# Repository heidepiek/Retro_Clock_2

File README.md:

# Retro Clock 2

This is a personal customized version of the original ESP32 Pacman Clock project.  
I've added some visual and functional enhancements to suit my own preferences.

### My additions:
- Blinking dots between hours and minutes
- Rectangle around the time
- Date and day display
- Text below the time: “ESP32 Pacman Clock”
- Pacman and ghost icons

The rest of this README reflects the original project, which deserves full credit for the excellent foundation.

# Retro_Clock_2
 Improved version of Retro_Clock
 1. Redesigned all of clock case parts with freeCAD. results in cleaner parts.
 2. All STL files are from freeCAD redesign.
 3. Minor firmware changes. Added menu items.
 4. PCB redesign to use better audio amplifier.
 
# Retro_Clock
This is a highly modified version of TechKiwiGadgets clock found on 

1. Instructables     https://www.instructables.com/ESP32-Pacman-Clock/
2. Makerbot Thingiverse (ESP32 Pacman Clock)    https://www.thingiverse.com/thing:5136672

Modifications:
1. Changed TFT display to an SPI version which has a much improved Touch interface.
2. Added SPIFFS to support files for data and images. This freed up memory and added flexability.
3. Added support for optional RTC (real time clock IC). Improves time keeping accuracy.
4. Added support for LDR (light dependent resistor) so that display is dimmed at night.
5. Added audio amplifier (LM386) and volume control via touch screen.
6. Redesigned user interface (Touch menu) to support added features.
7. Made many changes to firmware to improve speed and readability. 
8. Designed PCB to support above mentioned changes.
9. Redesigned 3D printed parts to support hardware changes.

TFT_eSPI library:
1. The TFT_eSPI library requires it be changed to support each particular build (unusal but that's way way it works).
2. The file User_Setup_Select.h specifies which setup file in the User_Setups directory is to be used.
3. Added to the User_Setups directory is the file Setup_Pacman_Clock.h which contains the specifies the configuration and features (Touch) used by this project.
4. Move the file "Setup_Pacman_Clock.h" into directory   ...Arduino/libraries/TFT_eSPI/User_Setups
5. Move the file "User_Setup_Select.h" into the directory    ...Arduino/libraries/TFT_eSPI   (replaces the existing User_Setup_Select.h file). 

Tools:
1. Arduino IDE 1.8.19, Board: DOIT ESP32 DEVKIT V1
2. Initialize SPIFFS using Arduino IDE  "Tools/ESP32 Sketch Data Upload" (which will initializee SPIFFS and upload all the files from the Data directory).
3. Creality Slicer, PLA, 0.2mm, no supports.

Additional Notes:
1. 	Arduino Sketch (IDE) Version 1.8.19
2.	Board Manager -> esp32 by Espressif Systems Version 1.0.6
3.	Libraries used:

		TFT_eSPI at version 2.5.0
		RTClib at version 2.1.1
		Wire at version 1.0.1
		SPIFFS at version 1.0
		FS at version 1.0
		XT_DAC_Audio
		Time at version 1.6.1
		Adafruit_BusIO at version 1.14.1
4.	TFT_eSPI setup file contains (see TFT_eSPI folder in Arduino/libraries):

		#define USER_SETUP_ID 900
		#define ILI9341_DRIVER
		#define TFT_MISO	19
		#define TFT_MOSI	23
		#define TFT_SCLK	18
		#define TFT_CS		15
		#define TFT_DC		4
		#define TFT_RST		2

		#define TOUCH_CS	5		// Required to enable Touch, getTouch()

		#define LOAD_GLCD
		#define LOAD_FONT2
		#define LOAD_FONT4
		#define LOAD FONT6
		#define LOAD_FONT7
		#define LOAD_FONT8
		#define LOAD_GFXFF
		#define SMOOTH_FONT

		#define SPI_FREQUENCY 27000000					// 27 MHz
		#define SPI_READ_FREQUENCY 20000000				// 20 MHz
		#define SPI_TOUCH_FREQUENCY 2500000				// 2.5 MHz

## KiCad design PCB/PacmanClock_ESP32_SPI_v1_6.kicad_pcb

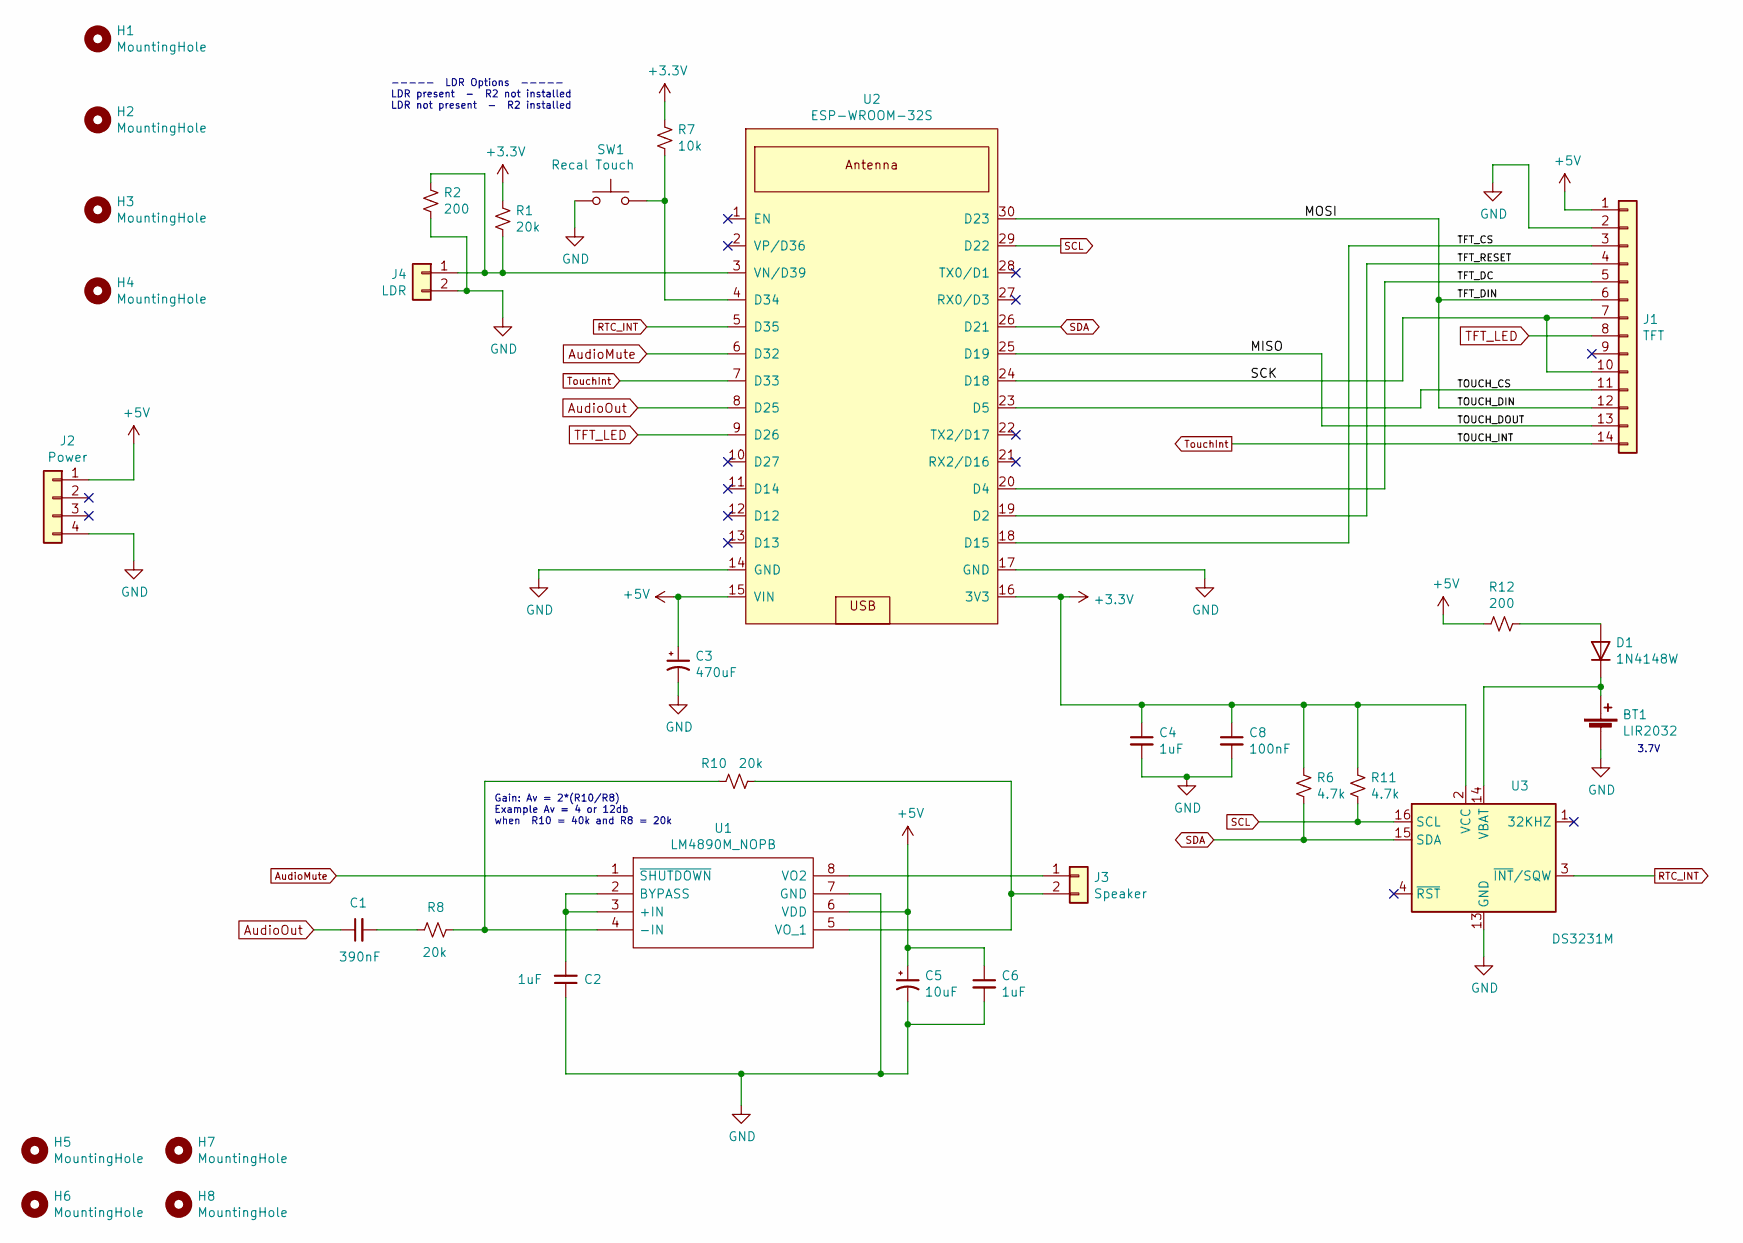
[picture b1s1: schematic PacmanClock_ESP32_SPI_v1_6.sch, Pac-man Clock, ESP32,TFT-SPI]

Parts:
BT1: LIR2032; 2032BatteryHolderHoriz
C1: 390nF; C_0805_2012Metric_Pad1.18x1.45mm_HandSolder
C2, C4: 1uF; C_1206_3216Metric_Pad1.33x1.80mm_HandSolder
C3: 470uF; CP_Radial_D8.0mm_P3.50mm
C5: 10uF; CP_Radial_D4.0mm_P1.50mm
C6: 1uF; C_0805_2012Metric_Pad1.18x1.45mm_HandSolder
C8: 100nF; C_0805_2012Metric_Pad1.18x1.45mm_HandSolder
D1: 1N4148W; D_SOD-123
H1, H2, H3, H4, H5, H6, H7, H8: MountingHole; MountingHole_2.7mm_M2.5_DIN965
J1: TFT; PinSocket_1x14_P2.54mm_Vertical
J2: Power; JST_XH_B4B-XH-A_1x04_P2.50mm_Vertical
J3: Speaker; JST_XH_B2B-XH-A_1x02_P2.50mm_Vertical
J4: LDR; JST_XH_B2B-XH-A_1x02_P2.50mm_Vertical
R1, R8, R10: 20k; R_0805_2012Metric_Pad1.20x1.40mm_HandSolder
R2, R12: 200; R_0805_2012Metric_Pad1.20x1.40mm_HandSolder
R6, R11: 4.7k; R_0805_2012Metric_Pad1.20x1.40mm_HandSolder
R7: 10k; R_0805_2012Metric_Pad1.20x1.40mm_HandSolder
SW1: Recal Touch; FSM2JRT_gm
U1: LM4890M_NOPB; SOIC-8_3.9x4.9mm_P1.27mm; Manufacturer_Part_Number LM4890M/NOPB; Mouser Part Number 926-LM4890M/NOPB
U2: ESP-WROOM-32S
U3: DS3231M; SOIC-16W_7.5x10.3mm_P1.27mm

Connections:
+3V3: C4.1, C8.1, R1.1, R6.1, R7.1, R11.1, U2.16 (3V3), U3.2 (VCC)
+5V: C3.1, C5.1, C6.1, J1.1, J2.1, R12.2, U1.6 (VDD), U2.15 (VIN)
/MISO: J1.13, U2.25 (D19)
/MOSI: J1.6, J1.12, U2.30 (D23)
/SCK: J1.7, J1.10, U2.24 (D18)
/TFT_CS: J1.3, U2.18 (D15)
/TFT_DC: J1.5, U2.20 (D4)
/TFT_RESET: J1.4, U2.19 (D2)
/TOUCH_CS: J1.11, U2.23 (D5)
AudioMute: U1.1 (~SHUTDOWN), U2.6 (D32)
AudioOut: C1.1, U2.8 (D25)
GND: BT1.2 (-), C2.1, C3.2, C4.2, C5.2, C6.2, C8.2, J1.2, J2.4, J4.2, R2.2, SW1.1, U1.7 (GND), U2.14 (GND), U2.17 (GND), U3.5 (GND), U3.6 (GND), U3.7 (GND), U3.8 (GND), U3.9 (GND), U3.10 (GND), U3.11 (GND), U3.12 (GND), U3.13 (GND)
unnamed: BT1.1 (+), D1.1 (K), U3.14 (VBAT)
unnamed: C1.2, R8.2
unnamed: C2.2, U1.2 (BYPASS), U1.3 (+IN)
unnamed: D1.2 (A), R12.1
unnamed: J3.1, U1.8 (VO2)
unnamed: J3.2, R10.2, U1.5 (VO_1)
unnamed: J4.1, R1.2, R2.1, U2.3 (VN/D39)
unnamed: R7.2, SW1.2, U2.4 (D34)
unnamed: R8.1, R10.1, U1.4 (-IN)
RTC_INT: U2.5 (D35), U3.3 (~INT~/SQW)
SCL: R11.2, U2.29 (D22), U3.16 (SCL)
SDA: R6.2, U2.26 (D21), U3.15 (SDA)
TFT_LED: J1.8, U2.9 (D26)
TouchInt: J1.14, U2.7 (D33)

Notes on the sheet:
3.7V
Gain: Av = 2*(R10/R8) Example Av = 4 or 12db when R10 = 40k and R8 = 20k
----- LDR Options ----- LDR present - R2 not installed LDR not present - R2 installed

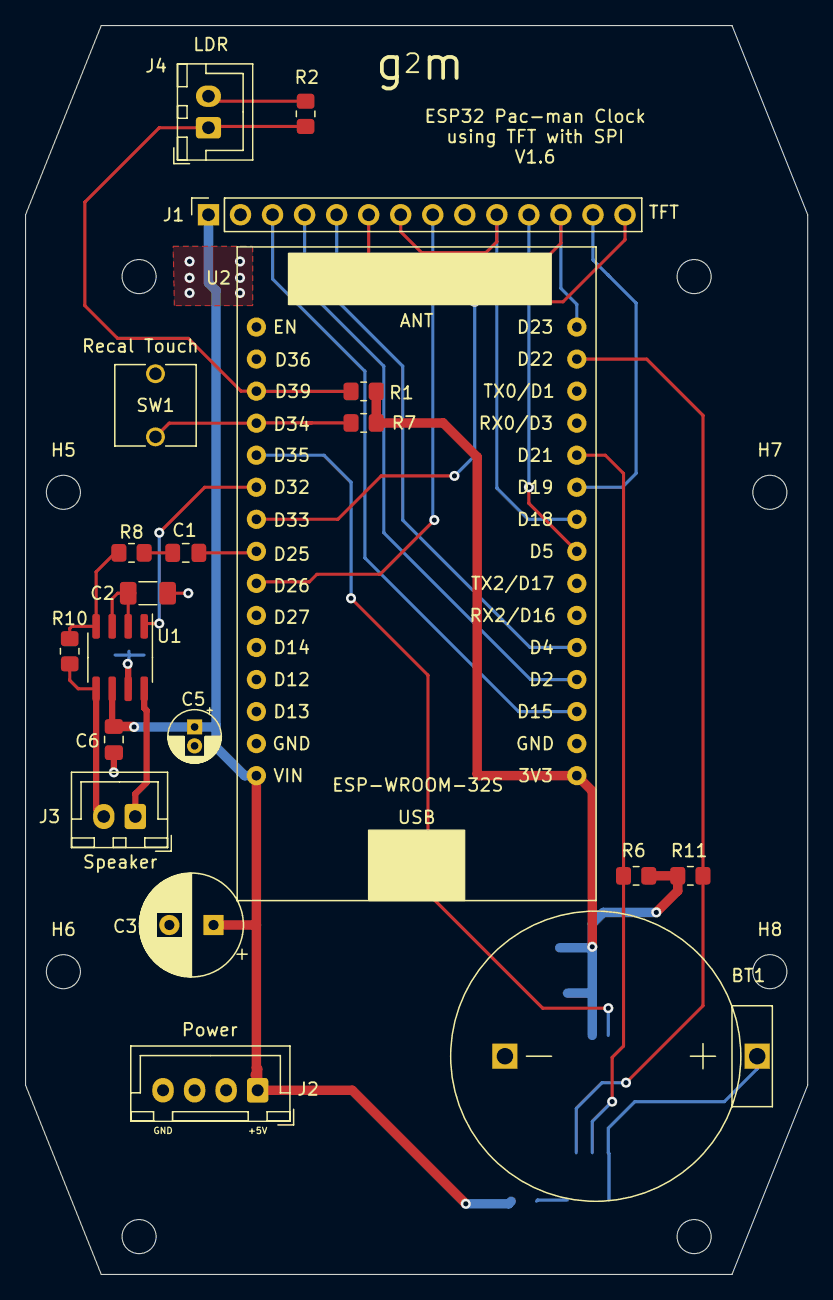
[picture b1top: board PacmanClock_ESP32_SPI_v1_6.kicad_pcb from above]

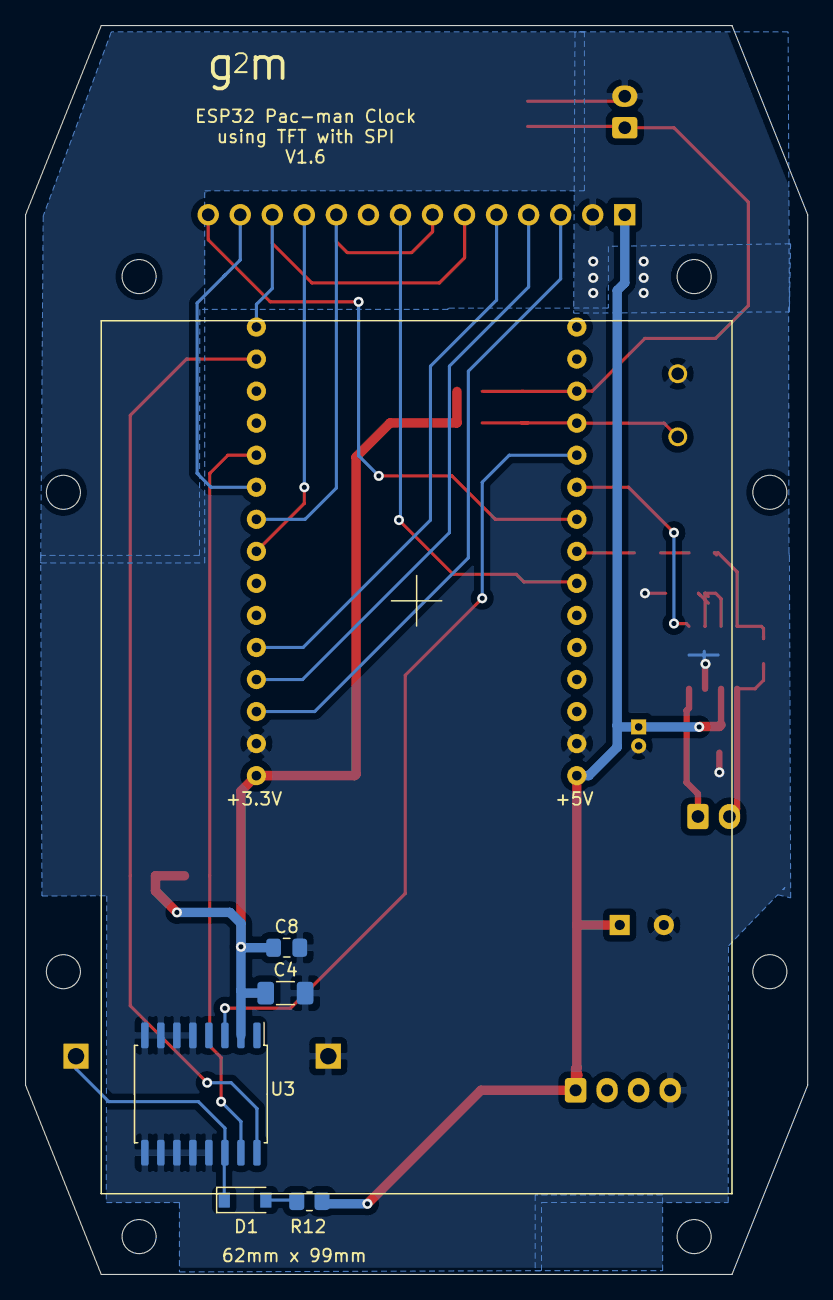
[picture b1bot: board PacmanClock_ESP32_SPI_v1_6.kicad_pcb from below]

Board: 2 copper layers, 62.0 x 99.0 mm, 33 parts (5 on the bottom side), 26 nets.

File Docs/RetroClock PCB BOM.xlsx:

Retro Clock 2
Component Count: | 33
Ref | Value | Footprint | Amazon (search) | Notes
BT1 | Holder | KiCab_g2m_Lib:2032BatteryHolderHoriz |  | See note on U3,. Used battery holder from DS3231 board.
C1 | 390nF | Capacitor_SMD:C_0805_2012Metric_Pad | 0805 SMD Capacitor Assorted Kit 1pF-1uF Chip Ceramic Capacitor
C2 | 1uF | Capacitor_SMD:C_1206_3216Metric_Pad | 1206 SMD Capacitor Assorted Kit 10P-22UF Chip Ceramic Capacitor
C3 | 470uF | Capacitor_THT:CP_Radial_D8.0mm_P3.50mm | lectrolytic Capacitor 470uF 16V with Aluminum Radial Leads 470UF-16V-8X12
C4 | 1uF | Capacitor_SMD:C_1206_3216Metric_Pad | 1206 SMD Capacitor Assorted Kit 10P-22UF Chip Ceramic Capacitor
C5 | 10uF | Capacitor_THT:CP_Radial_D4.0mm_P1.50mm | Electrolytic Capacitor 10uF 25V with Aluminum Radial Leads 10UF-25V-4X7
C6 | 1uF | Capacitor_SMD:C_0805_2012Metric_Pad | 0805 SMD Capacitor Assorted Kit 1pF-1uF Chip Ceramic Capacitor
C8 | 100nF | Capacitor_SMD:C_0805_2012Metric_Pad | 0805 SMD Capacitor Assorted Kit 1pF-1uF Chip Ceramic Capacitor
D1 | 1N4148W | Diode_SMD:D_SOD-123 |  | See U3. Used diode from DS3231 board.
H1 | MountingHole | MountingHole:MountingHole_2.7mm_M2.5_DIN965
H2 | MountingHole | MountingHole:MountingHole_2.7mm_M2.5_DIN965
H3 | MountingHole | MountingHole:MountingHole_2.7mm_M2.5_DIN965
H4 | MountingHole | MountingHole:MountingHole_2.7mm_M2.5_DIN965
H5 | MountingHole | MountingHole:MountingHole_2.7mm_M2.5_DIN965
H6 | MountingHole | MountingHole:MountingHole_2.7mm_M2.5_DIN965
H7 | MountingHole | MountingHole:MountingHole_2.7mm_M2.5_DIN965
H8 | MountingHole | MountingHole:MountingHole_2.7mm_M2.5_DIN965
J1 | TFT Connector | Connector_PinSocket_2.54mm:PinSocket_1x14_P2.54mm_Vertical | 40 Pin 2.54mm Single Row Straight Female PCB Header Connector Strip | Cut strip to required length - 14 pins.
J2 | Power | Connector_JST:JST_XH_B4B-XH-A_1x04_P2.50mm_Vertical | JST-XH 2.54mm Connector Kit, 2.54mm Male and Female 2/3/4/5/6 Pin Header Housin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
J3 | Speaker | Connector_JST:JST_XH_B2B-XH-A_1x02_P2.50mm_Vertical | JST-XH 2.54mm Connector Kit, 2.54mm Male and Female 2/3/4/5/6 Pin Header Housin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
J4 | LDR | Connector_JST:JST_XH_B2B-XH-A_1x02_P2.50mm_Vertical | JST-XH 2.54mm Connector Kit, 2.54mm Male and Female 2/3/4/5/6 Pin Header Housin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
R1 | 20k | Resistor_SMD:R_0805_2012Metric_Pad | 0805 SMD Resistor Kit 0-10M Ω ohm
R2 | 200 | Resistor_SMD:R_0805_2012Metric_Pad | 0805 SMD Resistor Kit 0-10M Ω ohm | Only installed if LDR option is not used.
R6 | 4.7k | Resistor_SMD:R_0805_2012Metric_Pad | 0805 SMD Resistor Kit 0-10M Ω ohm
R7 | 10k | Resistor_SMD:R_0805_2012Metric_Pad | 0805 SMD Resistor Kit 0-10M Ω ohm
R8 | 20k | Resistor_SMD:R_0805_2012Metric_Pad | 0805 SMD Resistor Kit 0-10M Ω ohm
R10 | 20k | Resistor_SMD:R_0805_2012Metric_Pad | 0805 SMD Resistor Kit 0-10M Ω ohm
R11 | 4.7k | Resistor_SMD:R_0805_2012Metric_Pad | 0805 SMD Resistor Kit 0-10M Ω ohm
R12 | 200 | Resistor_SMD:R_0805_2012Metric_Pad | 0805 SMD Resistor Kit 0-10M Ω ohm
SW1 | Recal Touch | Tactile-switch:FSM2JRT_gm | 6x6x7mm 2 Pin Panel PCB Momentary Tactile Tact Push Button Switch Through Hole 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
U1 | LM4890M_NOPB | Package_SO:SOIC-8_3.9x4.9mm_P1.27mm |  | Mouser: 926-LM4890M/NOPB
U2 | ESP-WROOM-32S | If Socketed (recommended) - uses two of the following connectors Connector_PinS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 | 40 Pin 2.54mm Single Row Straight Female PCB Header Connector Strip | Cut strip to required length - 15 pins. Quantity 2.
U3 | DS3231M | Package_SO:SOIC-16W_7.5x10.3mm_P1.27mm | DS3231 AT24C32 Clock Module Real Time Clock Module IIC RTC Module | Ordering from Amazon is much less expensive. Although you will need to remove t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
Plug-in Devices
Battery | LIR2032 | Rechargeable 2032 Battery, 3.7V | LIR2032 Rechargeable Batteries 3.7V with High Capacity 70mA
TFT |  | 2.8 inch TFT with Touch, SPI interface. | ILI9341 2.8" SPI TFT LCD Display Touch Panel 240X320
ESP32S | ESP32S | ESP32S Module - 30 pins (2 rows of 15 pins) | ESP-WROOM-32 ESP32 ESP-32S Development Board 2.4GHz Dual-Mode WiFi + Bluetooth 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
Hardware
Screws - 6mm Qty 9 |  | Torx Plus Rounded Head Thread-Forming Screws for Plastic, Zinc-Plated Steel, M2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 | McMaster-Carr mcmaster.com | 4 to mount Bezel Trim to Bezel 4 to mount PCB to Bezel 1 to mount USB Bracket t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
Screws - 8mm Qty 2 |  | Torx Plus Rounded Head Thread-Forming Screws for Plastic, Zinc-Plated Steel, M2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 | McMaster-Carr mcmaster.com | 2 to mount Rear Case to Bezel
Screws - 10mm Qty 2 |  | Torx Plus Rounded Head Thread-Forming Screws for Plastic, Zinc-Plated Steel, M2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 | McMaster-Carr mcmaster.com | 2 to mount USB Lock and USB Connector board to USB bracket
Glue |  | Either hot-glue or super-glue Decal to Bezel. Hot glue LDR to Decal.

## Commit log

2023-11-11 Initial Release of Retro Clock 2
    See Readme for details.
2023-11-12 Update
    Added Clock Schematic file and updated PCB Schematic file
2023-11-12 Added BOM
    Added BOM to DOC directory
2025-08-03 Update ESP32_Pacman_Clock_V1_9.ino
    Add blinking dots, date/time frame, icons, and Pacman text
2025-08-03 Add custom libraries folder
2025-08-03 Add demo GIF of Pacman Clock
2025-08-03 Add GIF and custom intro to README
